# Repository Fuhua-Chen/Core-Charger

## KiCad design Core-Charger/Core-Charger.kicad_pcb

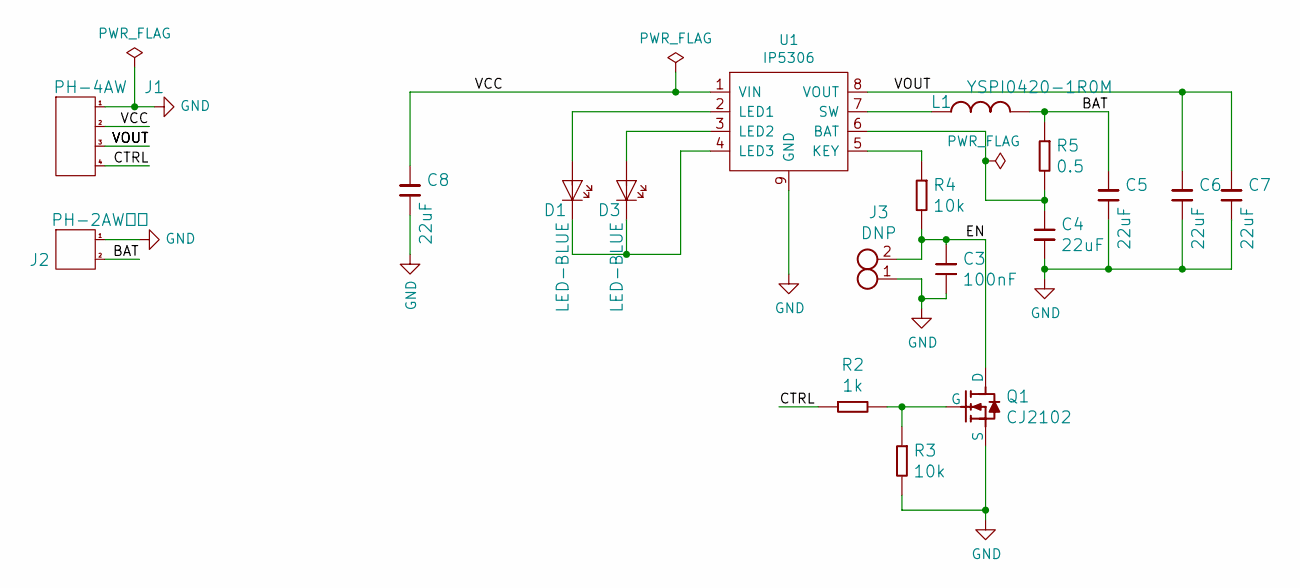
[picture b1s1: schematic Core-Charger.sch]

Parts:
C3: 100nF; C_0402_1005Metric; PartNumber 0402B104K500NT
C4, C5, C6, C7, C8: 22uF; C_0805_2012Metric; PartNumber CL21A226MAQNNNE
D1, D3: LED-BLUE; LED_0603_1608Metric; PartNumber 19-217/BHC-ZL1M2RY/3T
J1: PH-4AW; JST_PH_S4B-PH-K_1x04_P2.00mm_Horizontal; PartNumber PH-4AW
J2: PH-2AW环保; JST_PH_S2B-PH-K_1x02_P2.00mm_Horizontal; PartNumber PH-2AW环保
J3: DNP; PinHeader_1x02_P2.00mm_Vertical
L1: YSPI0420-1R0M; L_Bourns-SRN4018; PartNumber YSPI0420-1R0M
Q1: CJ2102; SOT-323_SC-70; PartNumber CJ2102
R2: 1k; R_0402_1005Metric; PartNumber 0402WGF1001TCE
R3, R4: 10k; R_0402_1005Metric; PartNumber 0402WGF1002TCE
R5: 0.5; R_0805_2012Metric; PartNumber 0805W8F500LT5E
U1: IP5306; SOIC-8-1EP_3.9x4.9mm_P1.27mm_EP2.29x3mm; PartNumber IP5306

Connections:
/BAT: C5.1, J2.2, L1.2, R5.1
/CTRL: J1.4, R2.1
/EN: C3.1, J3.2, Q1.3 (D), R4.2
/VCC: C8.1, J1.2, U1.1 (VIN)
/VOUT: C6.1, C7.1, J1.3, U1.8 (VOUT)
GND: C3.2, C4.2, C5.2, C6.2, C7.2, C8.2, J1.1, J2.1, J3.1, Q1.2 (S), R3.2, U1.9 (GND)
unnamed: C4.1, R5.2, U1.6 (BAT)
unnamed: D1.1, D3.1, U1.4 (LED3)
unnamed: D1.2, U1.2 (LED1)
unnamed: D3.2, U1.3 (LED2)
unnamed: L1.1, U1.7 (SW)
unnamed: Q1.1 (G), R2.2, R3.1
unnamed: R4.1, U1.5 (KEY)

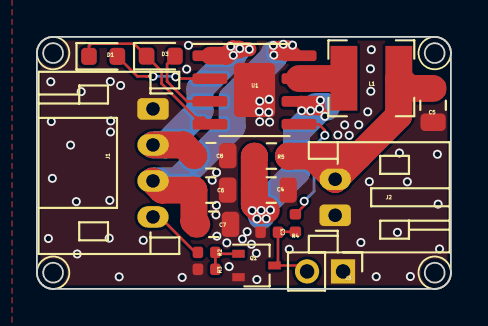
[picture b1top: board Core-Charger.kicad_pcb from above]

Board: 2 copper layers, 23.0 x 14.0 mm, 18 parts (0 on the bottom side), 13 nets.

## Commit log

2020-03-01 Core Modules Charger
